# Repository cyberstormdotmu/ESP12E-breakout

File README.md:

# ESP12E-breakout
A simple and open source ESP12E/ ESP8266 breakout board. You will need an external programmer to program the module but most of the components required to run the module are present. Made with KiCad.

To open the schematic and pcb file you will need KiCad.

Schematic pdf and PCB photos are provided.

breakoutesp12e.zip is a gerber file.

If you have any questions regarding the design or find any issues then just email me at nathan@cyberstorm.mu

Happy Hacking :)

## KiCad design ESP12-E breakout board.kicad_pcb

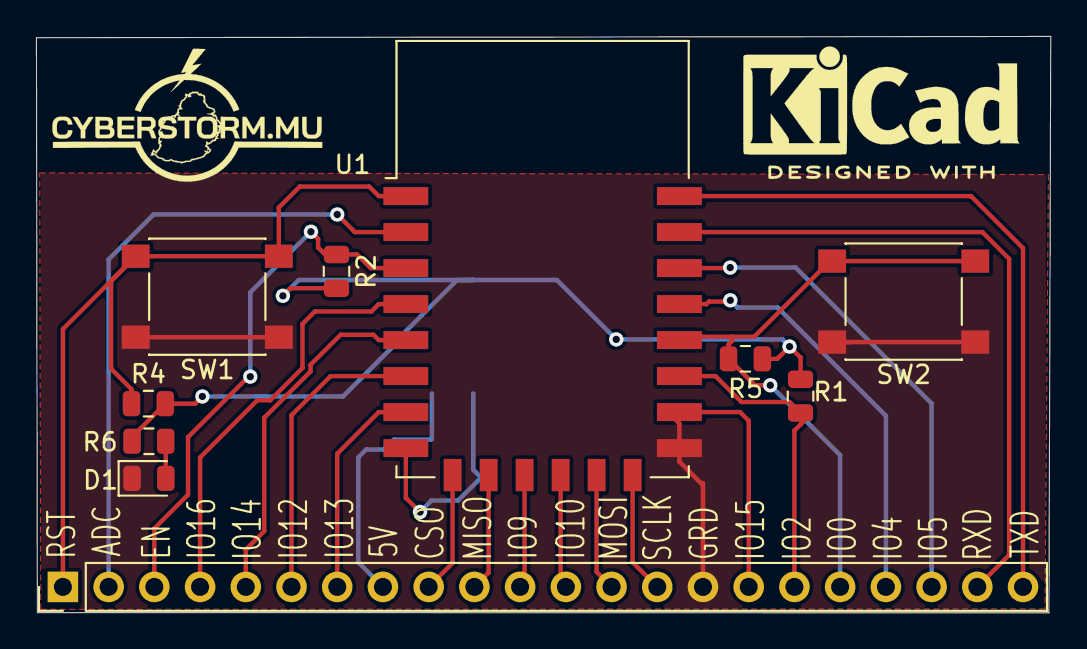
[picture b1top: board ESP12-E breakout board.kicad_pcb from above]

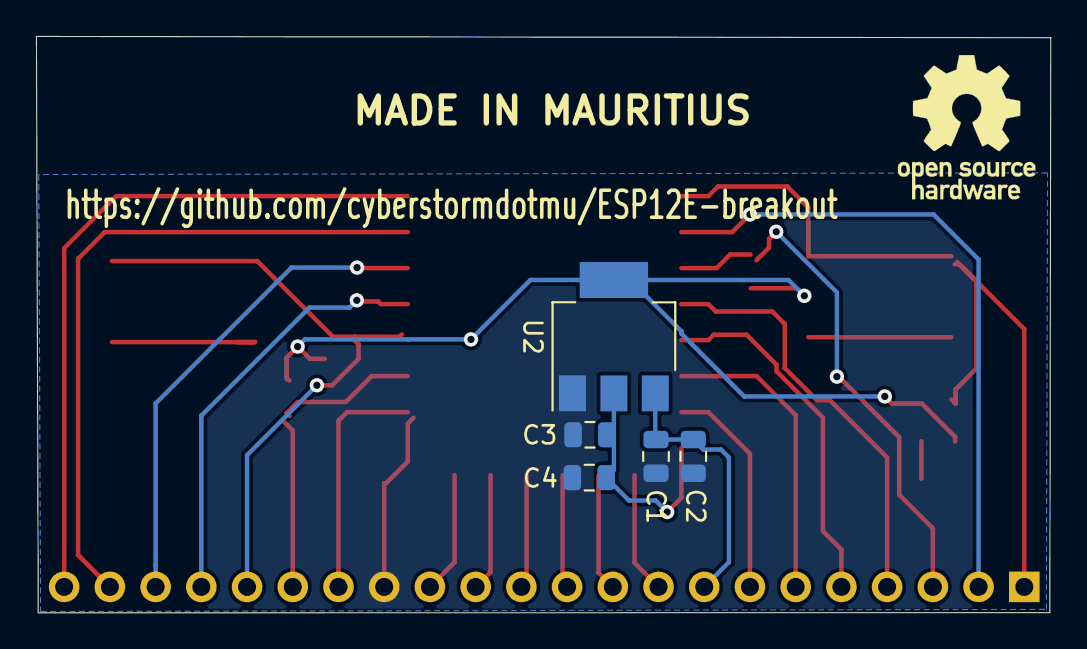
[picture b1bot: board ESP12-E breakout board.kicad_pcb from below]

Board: 2 copper layers, 56.3 x 32.0 mm, 15 parts (5 on the bottom side), 24 nets.

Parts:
C1, C3: 10uF; C_0805_2012Metric
C2, C4: 100nF; C_0805_2012Metric
D1: LED; LED_0805_2012Metric
J1: Conn_01x22_MountingPin; PinHeader_1x22_P2.54mm_Vertical
R1, R2, R4, R5: 1K; R_0805_2012Metric
R6: 220; R_0805_2012Metric
SW1, SW2: SW_Push; SW_Push_1P1T_NO_6x6mm_H9.5mm
U1: ESP-12E
U2: AMS1117-3.3; SOT-223-3_TabPin2

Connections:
3.3V: C3.1, C4.1, R1.2, R2.2, R4.2, R5.1, R6.2, U1.8, U2.2
5V: C1.1, C2.1, J1.8, U2.3
ADC: J1.2, U1.2
CSO: J1.9, U1.9
GND: C1.2, C2.2, C3.2, C4.2, D1.1, J1.15, SW1.1, SW2.1, U1.15, U2.1
IO0: J1.18, R5.2, SW2.2, U1.18
IO2: J1.17, R1.1
IO4: J1.19, U1.19
IO5: J1.20, U1.20
IO9: J1.11, U1.11
IO10: J1.12, U1.12
IO12: J1.6, U1.6
IO13: J1.7, U1.7
IO14: J1.5, U1.5
IO15: J1.16, U1.16
IO16: J1.4, U1.4
MISO: J1.10, U1.10
MOSI: J1.13, U1.13
unnamed: D1.2, R6.1
unnamed: R2.1, U1.3
RST: J1.1, R4.1, SW1.2, U1.1
RXD: J1.21, U1.21
SCLK: J1.14, U1.14
TXD: J1.22, U1.22

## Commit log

2019-05-30 Delete ESP12-E breakout board.sch
    Logo missing
2019-05-30 Add files via upload
    Logo added
2019-05-30 Add files via upload
    PDF of schematic ( logo not appearing )
2019-06-01 Add files via upload
    changes done to logos, schematics and added PCB layout
2019-06-01 Delete ESP12-E breakout board.kicad_pcb
    Random copper text on top layer
2019-06-01 Add files via upload
    Random copper text removed
2019-06-01 Add files via upload
    Gerber files added
2019-06-01 Update README.md
    Some extra info added
2019-06-01 Add files via upload
    Board and schematics modified due to some errors found during testing
2019-06-02 Update README.md
    Adding my contact details and something else
